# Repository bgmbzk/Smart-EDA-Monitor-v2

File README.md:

# ⚡ Smart EDA Stress Monitor v2.0

Bu proje, insan derisindeki elektriksel aktivite (Electrodermal Activity - EDA) değişimlerini ölçerek stres seviyesini analiz eden bir biyosensör prototipidir. v2.0 sürümünde, daha kararlı bir sinyal işleme katmanı ve modern bir PCB tasarımı hedeflenmiştir.

This project is a biosensor prototype that analyzes stress levels by measuring changes in Electrodermal Activity (EDA). In version 2.0, a more stable signal processing layer and a modern PCB design were targeted.

---

## 🚀 Öğrenme Yolculuğum / My Learning Journey
Bu proje, donanım tasarımı konusundaki **öğrenme ve gelişim sürecimin** önemli bir parçasıdır. İlk versiyondaki hatalardan ders çıkararak; daha temiz bir layout, optimize edilmiş sinyal yolları ve endüstriyel standartlara yakın bir PCB tasarımı hedefledim. Sürekli deneme ve iyileştirme üzerine kurulu bu süreçte, teorik bilgimi somut bir ürüne dönüştürmeyi amaçladım.

This project is a key part of my **continuous learning journey** in hardware design. By learning from previous iterations, I aimed for a cleaner layout, optimized signal paths, and a production-ready PCB design.

---

## 📸 Proje Görselleri / Project Visuals

### 1. 3D Model Tasarımı / 3D Model Design

*KiCad 3D Viewer kullanılarak hazırlanan, modern bileşen yerleşimine sahip nihai ürün prototipi.*

*(Final product prototype with modern component placement prepared using KiCad 3D Viewer.)*

### 2. Devre Şeması / Schematic Diagram

*LM358 Op-Amp sinyal koşullama ve L7805 voltaj regülatör katmanlarını içeren elektriksel tasarım.*

*(Electrical design including LM358 Op-Amp signal conditioning and L7805 voltage regulator stages.)*

### 3. PCB Yolları ve Yerleşim / PCB Layout & Routing

*Gürültü bağışıklığı için optimize edilmiş, kompakt PCB tasarımı. Sinyal bütünlüğü için ground plane uygulaması yapılmıştır.*

*(Compact PCB design optimized for noise immunity, featuring a ground plane for signal integrity.)*

---

## 🛠 Teknik Detaylar / Technical Details

### Donanım Bileşenleri / Hardware Components:
- **MCU:** Arduino Nano (ATmega328P)
- **Amplifier:** LM358 Op-Amp (Sinyal yükseltme ve aktif filtreleme için / For signal amplification and active filtering)
- **Power Management:** L7805 Voltage Regulator (Stabil 5V çıkış sağlar / Provides stable 5V output)
- **Sensor:** Deri direnci değişimlerini voltaj bölücü prensibiyle okuyan elektrotlar / Electrodes working with voltage divider principle.

### Tasarım Kararları / Design Decisions:
- **Iterative Improvement:** Tasarım, daha iyi bir estetik ve teknik kararlılık için yeniden revize edilmiştir.
- **Signal Quality:** Hassas analog yollar, paraziti önlemek adına mümkün olduğunca kısa tutulmuştur.

---

## 💻 Yazılım Mantığı / Software Logic

Arduino, LM358'den gelen yükseltilmiş analog veriyi **A0** pini üzerinden okur. / Arduino reads the amplified analog data from the LM358 via the **A0** pin.

```cpp
void setup() {
  Serial.begin(9600); // Seri haberleşme başlatıldı / Serial communication started
}

void loop() {
  int sensorValue = analogRead(A0); // A0 pininden veri oku / Read data from A0 pin
  Serial.println(sensorValue);      // Veriyi gönder / Send data for plotting
  delay(50);                        // Akıcı bir izleme için gecikme / Delay for smooth monitoring
}

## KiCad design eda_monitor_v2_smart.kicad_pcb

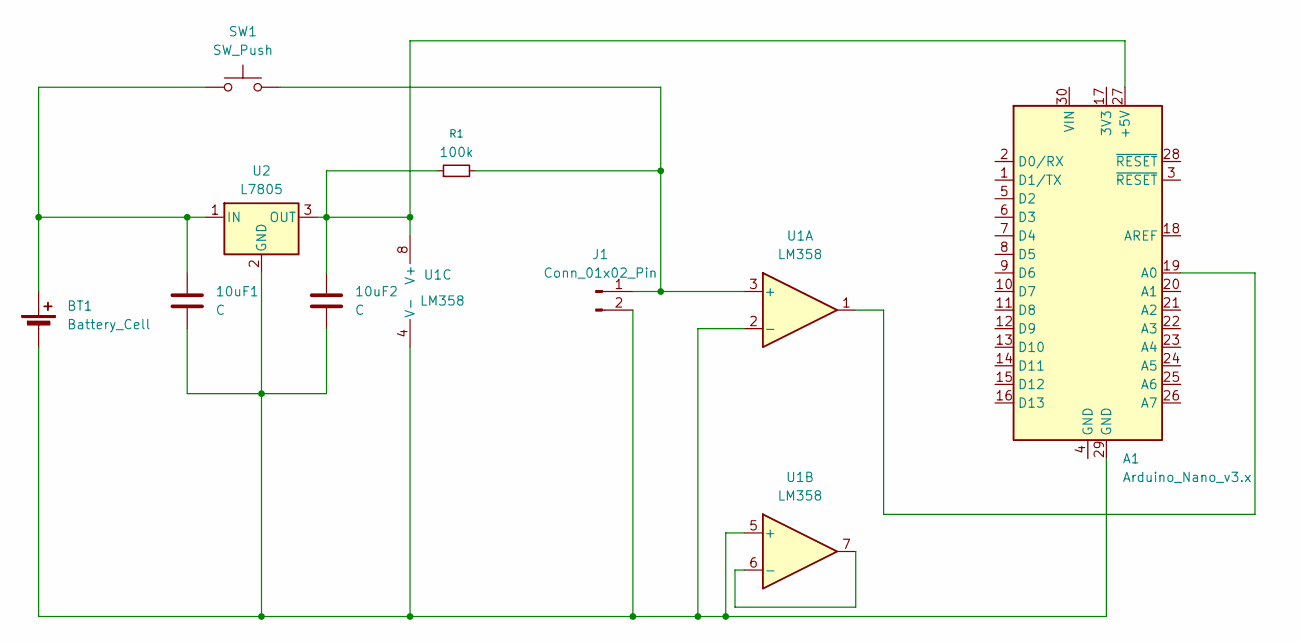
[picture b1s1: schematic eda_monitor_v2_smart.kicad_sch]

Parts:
10uF1, 10uF2: C; CP_Radial_D5.0mm_P2.50mm
A1: Arduino_Nano_v3.x; Arduino_Nano
BT1: Battery_Cell; PinHeader_1x02_P2.54mm_Vertical
J1: Conn_01x02_Pin; PinHeader_1x02_P2.54mm_Vertical
R1: 100k; R_Axial_DIN0207_L6.3mm_D2.5mm_P10.16mm_Horizontal
SW1: SW_Push; SW_Slide_SPDT_Straight_CK_OS102011MS2Q
U1: LM358; DIP-8_W7.62mm
U2: L7805; TO-220-3_Vertical

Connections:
unnamed: 10uF2.1, A1.27 (+5V), R1.1, U1.8 (V+), U2.3 (OUT)
unnamed: A1.19 (A0), U1.1
unnamed: 10uF1.1, BT1.1 (+), SW1.1, U2.1 (IN)
unnamed: 10uF1.2, 10uF2.2, A1.29 (GND), BT1.2 (-), J1.2, U1.2 (-), U1.4 (V-), U1.5 (+), U2.2 (GND)
unnamed: J1.1, R1.2, SW1.2, U1.3 (+)
unnamed: U1.6 (-), U1.7

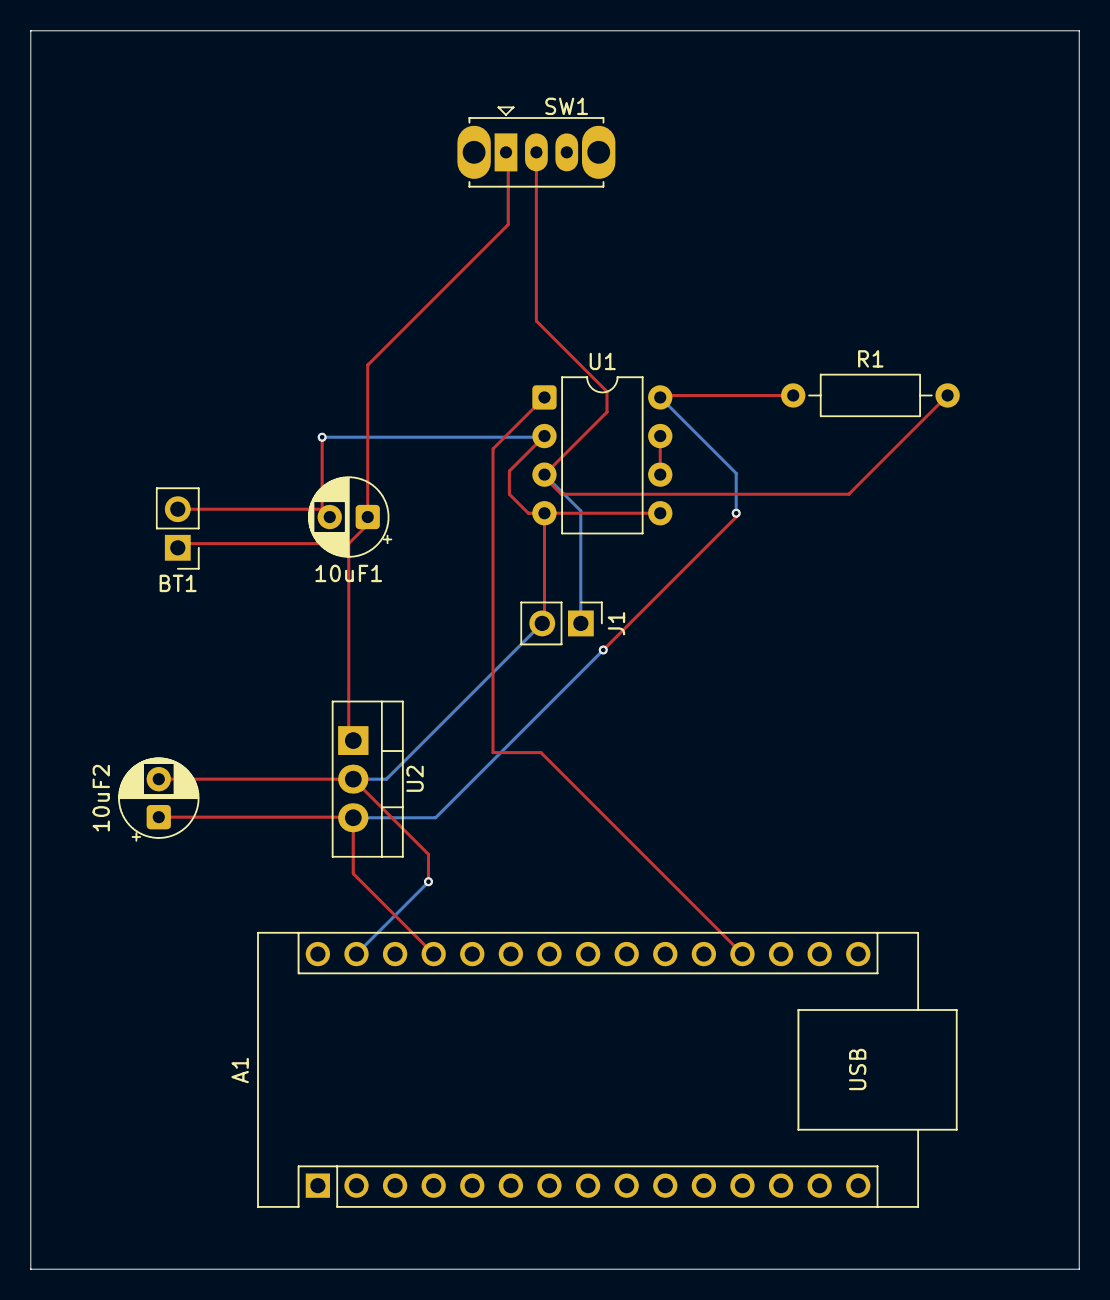
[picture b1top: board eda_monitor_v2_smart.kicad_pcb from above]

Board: 2 copper layers, 69.0 x 81.5 mm, 9 parts (0 on the bottom side), 6 nets.

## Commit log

2026-04-04 Enhance README with PCB layout details
    Added a description for the PCB layout section.
